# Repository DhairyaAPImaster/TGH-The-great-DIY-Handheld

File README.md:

# TGH - THE GREAT (DIY) HANDHELD
So yeah this is me trying to make my own custom retro handheld gaming device with a custom pcb powered by a pi zero 2w.

**BTW NOTE:** the case shall be printed by someone who was willing to print it from the slack channel - #printing-legion.

***very VERY IMPORTANT NOTE TO MACONDO REVIWER ---> SO IN THE BOM U MIGHT SEE THAT THE QTY OF SOME OF THE COMPONENTS FROM ROBU.IN IS MORE THAN REQUIRED THIS IS BECAUSE ROBU.IN HAS A MINIMUM ORDER QTY OF 10 INDIAN RUPEES PER COMPONENT SO HENCE I HAD TO LIKE INCREASE THE QTY OF SOME OF THE PASIVE COMPOENNTS TO LIKE FOLLOW THIS. BTW ITS STILL LIKE WAY WAY CHEAPER THAN JLCPCB'S PCBA THAT WOULD HAVE BROUGHT THE TOTAL COST TO 199.56 USD EXCLUDING TAX (I CHECKED)***

## project layout

```
.
├── `Assembly Layered.step`
├── `Assembly.step`
├── `wiring diagram.png`
├── `Custom Firmware!!!!!!!!!!/`
│   ├── `Launcher.py`
│   ├── `roms/`
│   │   ├── `GB/`
│   │   ├── `GBA/`
│   │   ├── `GBC/`
│   │   ├── `GEN/`
│   │   ├── `NES/`
│   │   ├── `SMS/`
│   │   └── `SNES/`
│   ├── `saves/`
│   └── `states/`
├── `production files/`
│   ├── `CAD/`
│   └── `PCB/`
│       ├── `MAIN PANELISED PCB (TO BE MANUFACTURED)/`
│       ├── `Mother board (not to be manufactured)/`
│       ├── `left daughter board (not to be manufactured)/`
│       └── `right daughter board (not to be manufactured)/`
└── `src/`
		├── `FreeCAD/`
		└── `PCB/`

```

## quick specs
- Panelised PCB Dimensions - 339.82 mm x 102.32 mm
- the only KiCAD plugin i used was KiKit to panelise the board, everything else was designed by me (this is my first major PCB project)

## WIRING DIAGRAM

## HOW TO RECREATE THIS PROJECT YOURSELF!!! 
- Step 1 - Basically Just Clone or downlaod this repo from github. U can do this by either going to the code button on this repo page and pressing download Zip or u can clone this Repo.
- Step 2 - Upload the gerbers zip file in JLCPCB (or any other manufacturer) Place order Page (u will need to sign up to order but can get a quote without signing up on jlcpcb)
- Step 3 - Change the colour of the PCB in the options JLC gives (if u use JLC PCB most of the times canging colours does not add any charge acc to what i know)
- Step 4 - Select PCBA if u want JLCPCB to assemble the PCB for you (though it is way more expensive than just soldering everything yourself.)
- Step 5 - Upload the CPL and BOM files.(if you are getting pcba)
- Step 6 - Recheck the position of all components
- Step 7 - Add to cart and order the PCB!! **(if you are soldering the components yourself you will need to buy them from some other place im mainly using robu.in and some components froma amzon and others)**
- Step 8 - If you dont have a 3D PRINTER jlcpcb has a 3d printing service too caled JLC3DP so u can upload the files for the case there and get it printed too but if u have a 3d printer you can just print it youreslf and save a lot of money.
- Step 9 - Order strong epoxy glue or superglue that does not cause harm to the 3d printed case material (I will be using FeviQuick as it should not cause harm to PLA in which the case will be printed)
- Step 10 - WAIT WAIT WAIT for your parts to be delhivered
- Step 11 - Once you have the PCB you will need to connect the daughter boards to the main motherboard using wires or an FFC connector i will be using solid code jumper wires since they are the easiest.
- Step 12 - If you are hand soldering the components you need to hand solder them according to the PCB Design that you can find by opening the project in kicad.
- Step 13 - Once you have all the parts ready (PCB, CASE and the appropriate Glue) place the PCB in the Case (you might have to trim the spacers down a bit as i made the spacers high so that they arent to small as i can always cut higher spacers down but can not extend spacers that are short.)  Use hot glue to secure the PCB onto the Spacers (btw if you have a smaller 3d printer you will have to like print the case in parts or diagonaly as it is slightly bigger than like the a1 mini and others of that size)
- Step 14 - Once the PCB is secured inside the case glue the Top Part of the Case shut after attatching the button caps onto the switches and adjusting the spacing of the screen.
- Step 15 - BOOM  THERE YOU HAVE IT THE PHYSICAL HARDWARE IS DONE NOW THE FIRMWARE.....

- Step 16 - To run the firmware first flash RASPBERRY PI OS onto the raspberry pi

- Step 17 - Put the microSD card into the Raspberry Pi Zero 2 W and power it on. Give it a little bit of time to boot for the first time. If you are using the Pi by itself for the initial setup, connect it to a display and keyboard so you can configure everything.

- Step 18 - Clone this repository onto the Raspberry PiThen enter the firmware folder:

	`TGH-The-great-DIY-Handheld/"Custom Firmware!!!!!!!!!!`

	The firmware folder should look something like this:
	```
	Custom Firmware!!!!!!!!!!
	├── Launcher.py
	├── roms/
	│   ├── GB/
	│   ├── GBA/
	│   ├── GBC/
	│   ├── GEN/
	│   ├── NES/
	│   ├── SMS/
	│   └── SNES/
	├── saves/
	└── states/
	```

 - Step 19 - If everything is working correctly, the TGH launcher should start.

 - ALMOST LAST STEP - ADD YOUR ROMS to there respective folders in the firmware folder
	Basically:

	Game Boy ROM → `GB/`

	Game Boy Advance ROM → `GBA/`

	Game Boy Color ROM → `GBC/`

	Genesis ROM → `GEN/`

	NES ROM → `NES/`

	Sega Master System ROM → `SMS/`

	SNES ROM → `SNES/`

- TRUE LAST STEP - CONNECT EVERYTHING TO THE CUSTOM PCB

- **RECOMMENDED** - Before closing the case, test:

Does the Pi boot?
Does the display work?
Does the launcher start?
Do the buttons work?
Do the joysticks work?
Does audio work?
Does the speaker work?
Does the headphone jack work?
Does the power system work?
Do games launch?
Do saves/states work?

If all of those work (IF U DO IT CORRECTLY IT WILL WORK) THEN..... 
## BOOM!!!! YOU HAVE A WORKING RETRO HANDHELD GAMING DEVICE!!!!!!

## BOM/BILL OF MATERIALS (PARTS I NEED FUNDING FOR)

| Name | Purpose | Quantity | Total Cost (USD) | Link | Distributor |
|---|---|---|---|---|---|
| PCB from JLCPCB  | it is the main PCB and will connect all components to each other. (btw JLCPCB has min order qty for PCB as 5 so yeah) | 5 | 18.4 | https://cart.jlcpcb.com/ | JLCPCB |
| Raspberry Pi Zero | its basically the core of the whole project it shall basically run everything. | 1 | 19.08 | https://robu.in/product/raspberry-pi-zero-wireless-wh-pre-soldered-header/ | robu.in |
| 5 Inch Touch Screen HDMI Interface TFT LCD | to display. | 1 | 26.18 | https://robu.in/product/5-inch-touch-screen-hdmi-interface-display-module-tft-lcd-800x480-raspberry-pi-2-model-b-touch-pen/ | robu.in |
| Mini HDMI To HDMI Cable | to connect pi to display | 1 | 1.08 | https://robu.in/product/mini-hdmi-hdmi-cable-1-8-meter-round-high-quality-copper-clad-steel-black/ | robu.in |
| 10 uF capacitor | to decouple more  | 15 | 0.14 | https://robu.in/product/cs2012x7r106m100nre-samwha-10v-10uf-x7r-%c2%b120-0805-multilayer-ceramic-capacitors-mlcc-smd-smt-rohs/ | robu.in |
| 100nF capacitor | to decouple | 20 | 0.14 | https://robu.in/product/tcc0805x7r104k500dt-cctc-smt-ceramic-capacitors-0805-x7r-104k100nf%c2%b110-rated-voltage50v-thickness0-85mmtape/ | robu.in |
| 6x6x5mm tactile switches | to well be used as switches and for the buttons controlling everything. | 10 | 0.14 | https://robu.in/product/6x6x5mm-tactile-push-button-switch-pack-of-20/ | robu.in |
| MAX98358ETE | audio amplifier | 1 | 2.62 | https://robu.in/product/1-month-warranty-560/ | robu.in |
| MT3608  IC | to take a lower DC voltage and steps it up to a higher, adjustable DC voltage | 2 | 0.28 | https://robu.in/product/mt3608-xian-aerosemi-tech-boost-type-adjustable-2a-2v24v-sot-23-6-dc-dc-converters-rohs/ | robu.in |
| 33 µH BOURNS-SRR1260-330M-Power Inductor (SMD) | to stores energy in a magnetic field and resists changes in electrical current. | 1 | 0.67 | https://robu.in/product/srr1260-330m-bourns-srr1260-330m-power-inductor-smd-33-%c2%b5h-3-a-shielded-2-8-a-srr1260-series/ | robu.in |
| SOD-123 Schottky Diodes ROHS | used to allow current to flow in one direction. | 2 | 0.12 | https://robu.in/product/1n5819w-kexin-40v-600mv1a-1a-sod-123-schottky-diodes-rohs/ | robu.in |
| 100 ohm resistor | to resist current | 25 | 0.12 | https://robu.in/product/rc0805jr-07100rl-yageo-res-thick-film-0805-100-ohm-5-0-125w1-8w-%c2%b1100ppm-c-pad-smd-t-r/ | robu.in |
| 4.7k ohm resistor | to resist  | 29 | 0.12 | https://robu.in/product/yageo-4-7k-ohm-1-4w-0805-surface-mount-resistor-pack-of-50/ | robu.in |
| 10k ohm resistor | im legit tired of writing the same thing again for all the resistor but anyways ---> IT resists the flow of current. | 20 | 0.12 | https://robu.in/product/rc0805fr-0710kl-yageo-res-thick-film-0805-10k-ohm-1-0-125w1-8w-%c2%b1100ppm-c-pad-smd-t-r/ | robu.in |
| 20k ohm resistor | u are not gonna belive what this does ---> IT resists the flow of current.... | 29 | 0.12 | https://robu.in/product/rc0805fr-0720kl-yageo-res-thick-film-0805-20k-ohm-1-0-125w1-8w-%c2%b1100ppm-c-pad-smd-t-r/ | robu.in |
| 33k ohm resistor | to resist!!!!! | 20 | 0.12 | https://robu.in/product/rc0805fr-0733kl-yageo-res-thick-film-0805-33k-ohm-1-0-125w1-8w-%c2%b1100ppm-c-pad-smd-t-r/ | robu.in |
| 100k ohm 0805 resistor | to resist flow of current? | 23 | 0.12 | https://robu.in/product/yageo-100k-ohm-1-2w-0805-surface-mount-resistor-pack-of-50/ | robu.in |
| D6.3xL11mm Aluminum Electrolytic Capacitors | its a capacitor dude like it provides capacitance (idk what do i write under Purpose) | 4 | 0.18 | https://robu.in/product/16yxf100mefct16-3x11-rubycon-100uf-16v-%c2%b120-plugind6-3xl11mm-aluminum-electrolytic-capacitors-leaded-rohs/ | robu.in |
| 22µF SMT 0805 capacitor | To provide capacitance | 10 | 0.18 | https://robu.in/product/tcc0805x5r226k100ft-cctc-smt-ceramic-capacitors-0805-x5r-226k22%c2%b5f%c2%b110-rated-voltage10v-thickness1-25mmtape/ | robu.in |
| TP4056 1A Li-Ion Battery Charging Board | To charge the battery  | 1 | 0.17 | https://robu.in/product/tp4056-1a-li-ion-battery-charging-board-micro-usb-with-current-protection-type-c-connector/ | Robu.in |
| 1mm Pitch Pin headers | These are seperate as the previous headers are not 1mm pitch pin headers. | 1 | 0.21 | https://robu.in/product/1-month-warranty-884/ | Robu.in |
| 3.5mm Female Audio Jack Connector  | to attach headphones | 1 | 0.47 | https://evelta.com/3-5mm-female-audio-jack-connector-6pin-1/ | Evelta.com |
| ADS1115IDGSR - 16-Bit ADC 2, 4 Input 1 Sigma-Delta IC VSSOP-10 | to convert analog voltage signals into digital data  | 1 | 1.94 | https://evelta.com/ads1115idgsr-16-bit-adc-2-4-input-1-sigma-delta-ic-vssop-10/ | Evelta.com |
| PS2 Game Joystick Module | For the Joysticks | 2 | 0.82 | https://www.flyrobo.in/ps2_game_joystick_module_for_arduino | FlyRobo |
| Male and Female Header Connector Strip, Pack of 10, Breakable Strip | For the pin Headers (btw this was a cheap pack of 10 and is actually cheaper than buying each header individually) | 1 | 1.27 | https://www.amazon.in/gp/product/B0FQP3SN7H/ref=ox_sc_act_image_8?smid=ATNZHHWX66S9H&psc=1 | Amazon |
| SPDT Slide Switch Right Angle | TO turn on and off | 1 | 1.0 | https://www.amazon.in/gp/product/B0B434R6QF/ref=ox_sc_act_image_7?smid=A2JDRZEGU1IDE2&psc=1 | Amazon |
| 0.5Watt Power Audio Speaker | For sound | 1 | 1.21 | https://www.amazon.in/gp/product/B07MTK843Z/ref=ox_sc_act_image_6?smid=AJ6SIZC8YQDZX&psc=1 | Amazon |
| Isopropyl Alcohol | For cleaning Board after soldering. | 1 | 2.95 | https://www.amazon.in/gp/product/B0DXLCF467/ref=ox_sc_act_image_5?smid=A66YHFPLB5NLO&th=1 | Amazon |
| Tactile Push Button Switch Caps | To button | 1 | 2.34 | https://www.amazon.in/gp/product/B0DCP7J7R7/ref=ox_sc_act_image_4?smid=AOG7U64E0DVL2&psc=1 | Amazon |
| Jumper Wires | For fine adjustment if required | 1 | 1.66 | https://www.amazon.in/gp/product/B0CPFCRCHB/ref=ox_sc_act_image_3?smid=AJ6SIZC8YQDZX&th=1 | Amazon |
| Solder  | to solder | 1 | 8.37 | https://www.amazon.in/gp/product/B084RZWVXY/ref=ox_sc_act_image_2?smid=AVIYBMAJK8N56&th=1 | Amazon |
| Soldering Flux | Helping to solder. | 1 | 0.84 | https://www.amazon.in/gp/product/B0FV8HHBTN/ref=ox_sc_act_image_1?smid=A366YFPXO3CTI5&psc=1 | Amazon |

## fab note
- so i plan on using JLCPCB to actually get my boards manufactured (i checked and for the size of this project's pcb getting the pcb from robu.in is way more expensive than jlcpcb) but will be ASSEMBLING THE COMPONENTS BY HAND!!!!

## pics from while i was designing it

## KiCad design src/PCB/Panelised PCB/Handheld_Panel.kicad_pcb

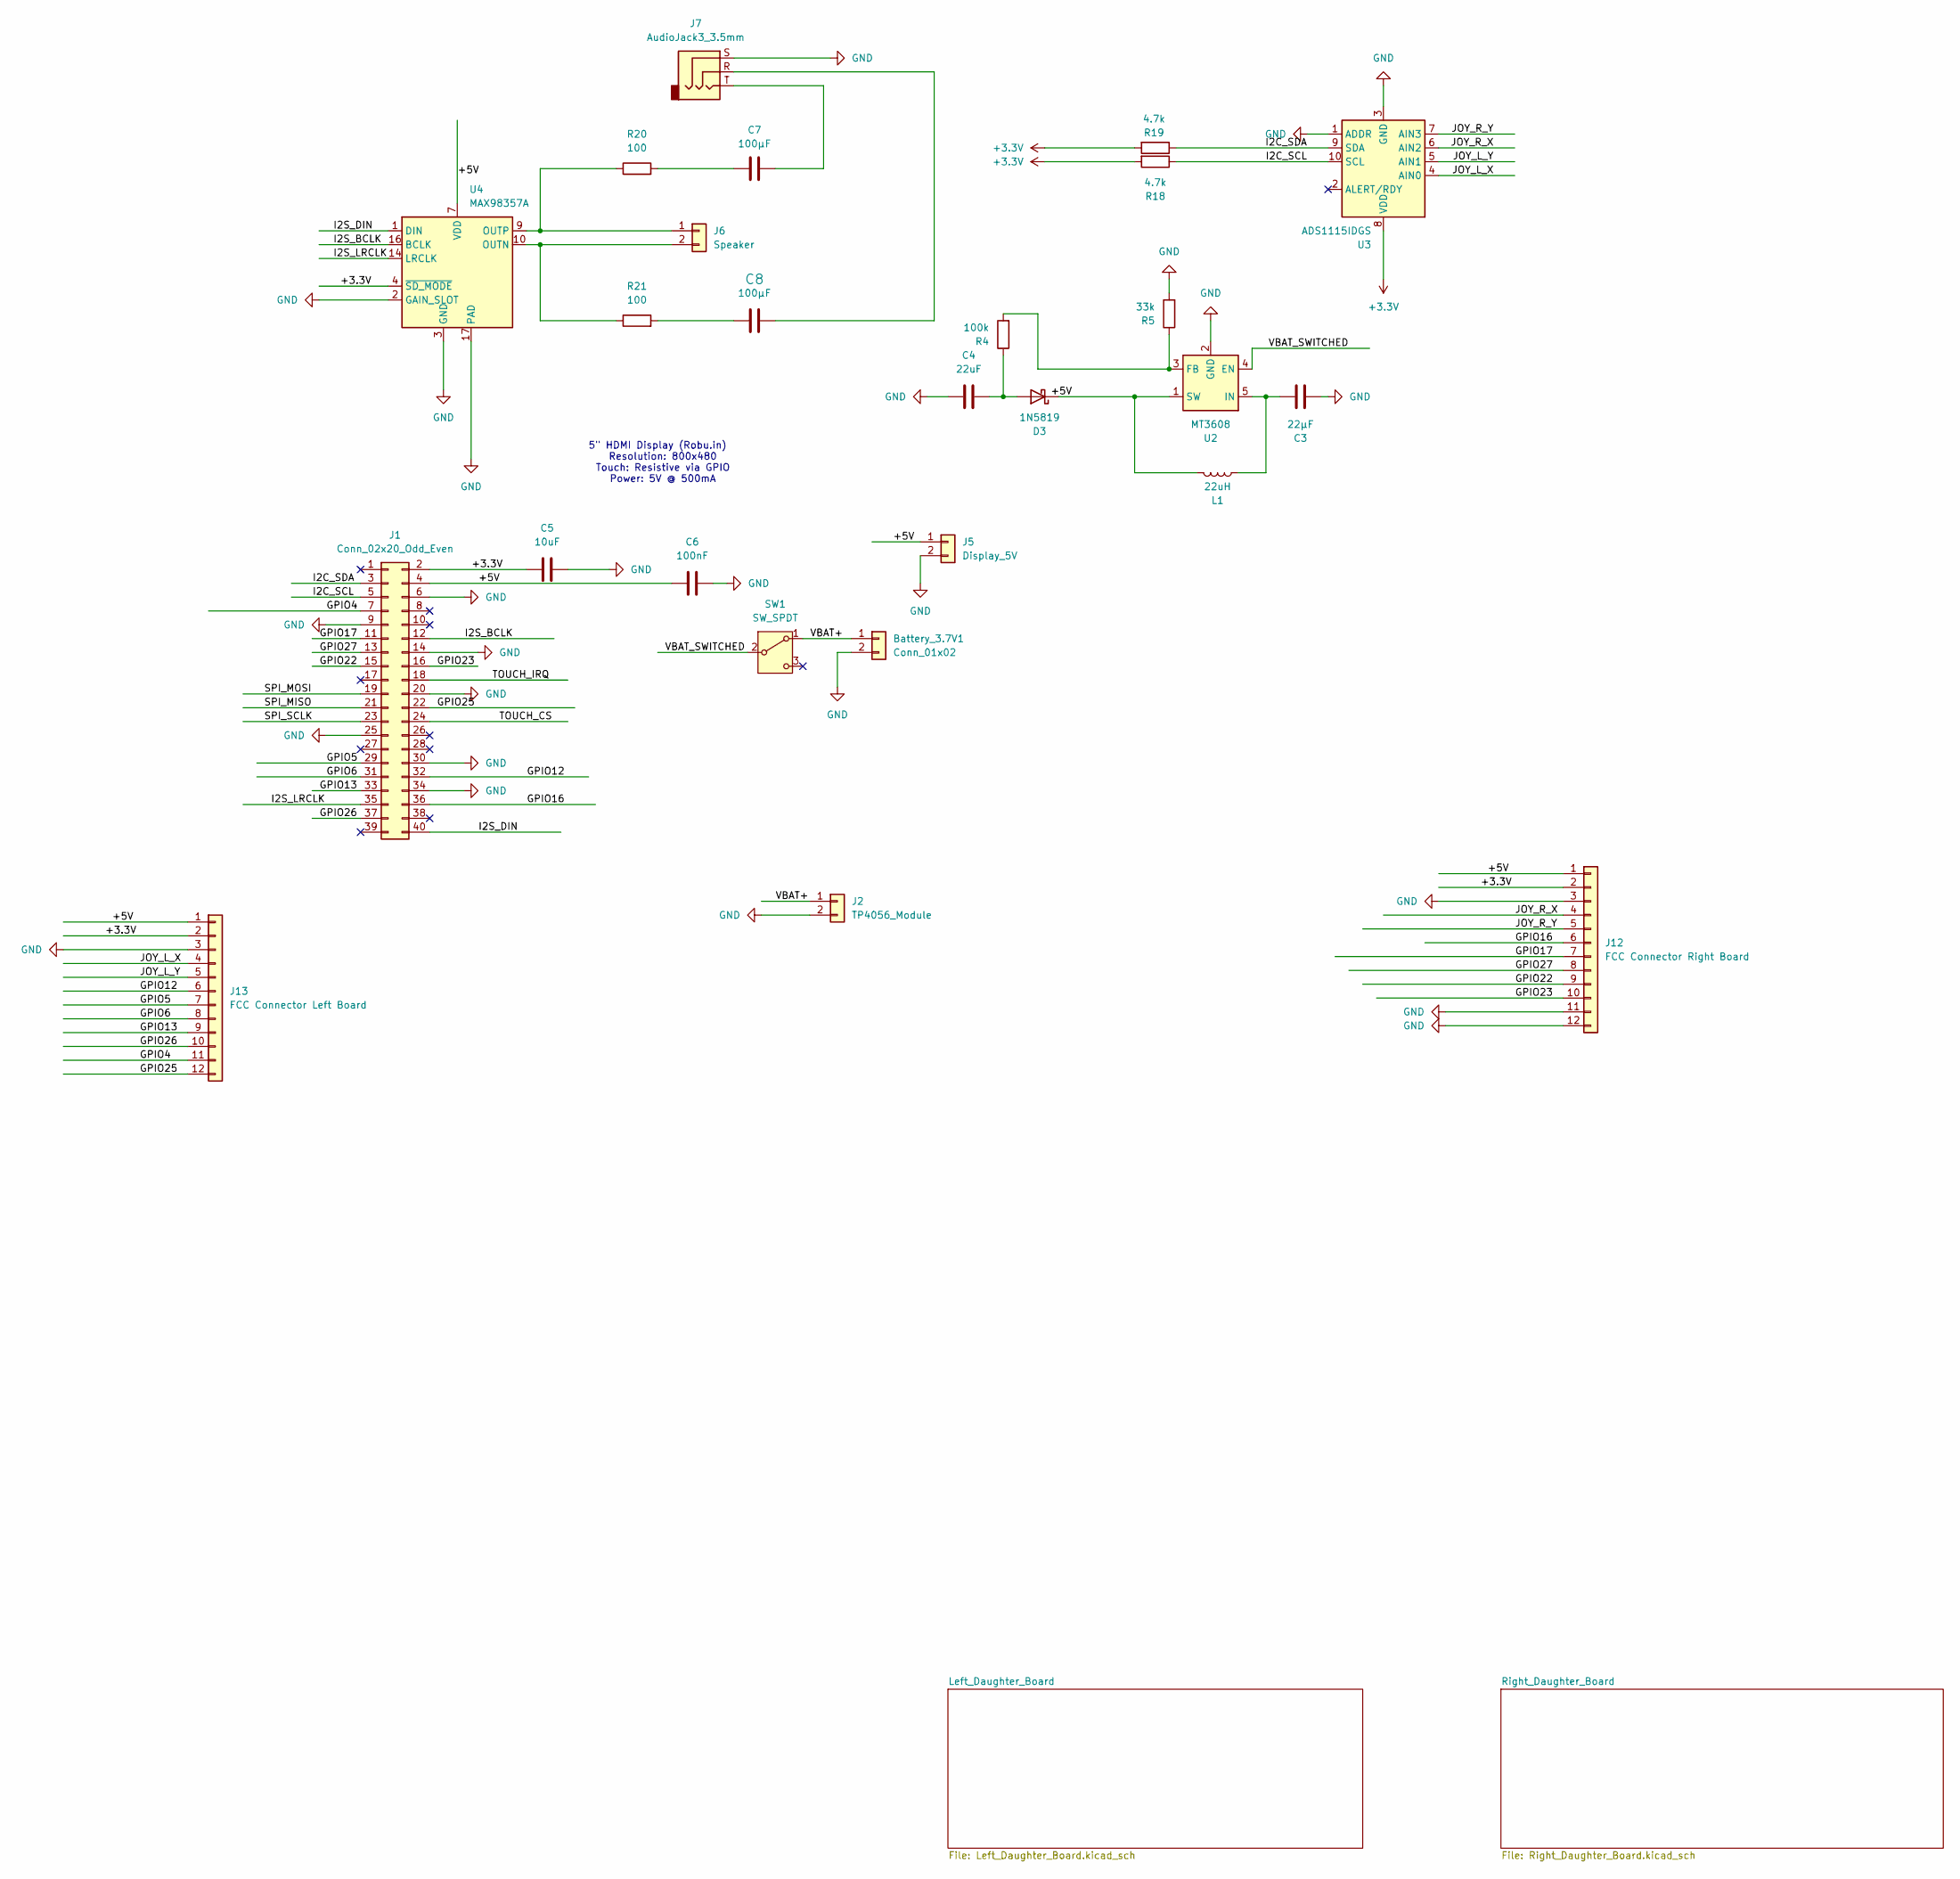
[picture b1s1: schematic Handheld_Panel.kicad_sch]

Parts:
Battery_3.7V1: Conn_01x02; PinHeader_1x02_P2.54mm_Vertical
C3: 22µF; C_0805_2012Metric
C4: 22uF; C_0805_2012Metric
C5: 10uF; C_0805_2012Metric
C6: 100nF; C_0805_2012Metric
C7, C8: 100µF; CP_Radial_D6.3mm_P2.50mm
D3: 1N5819; D_SOD-123
J1: Conn_02x20_Odd_Even; PinHeader_2x20_P2.54mm_Vertical
J2: TP4056_Module; PinHeader_1x02_P2.54mm_Vertical
J5: Display_5V; PinHeader_1x02_P2.54mm_Vertical
J6: Speaker; PinHeader_1x02_P2.54mm_Vertical
J7: AudioJack3_3.5mm; Jack_3.5mm_CUI_SJ-3523-SMT_Horizontal
J12: FCC Connector Right Board; PinHeader_1x12_P1.00mm_Vertical
J13: FCC Connector Left Board; PinHeader_1x12_P1.00mm_Vertical
L1: 22uH; L_Bourns_SRR1260
R4: 100k; R_0805_2012Metric
R5: 33k; R_0805_2012Metric
R18, R19: 4.7k; R_0805_2012Metric
R20, R21: 100; R_0805_2012Metric
SW1: SW_SPDT; SW_Slide_SPDT_Angled_CK_OS102011MA1Q
U2: MT3608; SOT-23-6
U3: ADS1115IDGS; TSSOP-10_3x3mm_P0.5mm
U4: MAX98357A; TQFN-16-1EP_3x3mm_P0.5mm_EP1.23x1.23mm

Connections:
+3.3V: C5.1, J1.2, J12.2, J13.2, R18.2, R19.2, U3.8 (VDD), U4.4 (~SD_MODE); also elsewhere on the board
/+5V: C6.1, D3.1 (K), J1.4, J5.1, J12.1, J13.1, L1.2, U2.1 (SW), U4.7 (VDD), U4.8 (VDD)
/GPIO4: J1.7, J13.11
/GPIO5: J1.29, J13.7
/GPIO6: J1.31, J13.8
/GPIO12: J1.32, J13.6
/GPIO13: J1.33, J13.9
/GPIO16: J1.36, J12.6
/GPIO17: J1.11, J12.7
/GPIO22: J1.15, J12.9
/GPIO23: J1.16, J12.10
/GPIO25: J1.22, J13.12
/GPIO26: J1.37, J13.10
/GPIO27: J1.13, J12.8
/I2C_SCL: J1.5, R18.1, U3.10 (SCL)
/I2C_SDA: J1.3, R19.1, U3.9 (SDA)
/I2S_BCLK: J1.12, U4.16 (BCLK)
/I2S_DIN: J1.40, U4.1 (DIN)
/I2S_LRCLK: J1.35, U4.14 (LRCLK)
/JOY_L_X: J13.4, U3.4 (AIN0)
/JOY_L_Y: J13.5, U3.5 (AIN1)
/JOY_R_X: J12.4, U3.6 (AIN2)
/JOY_R_Y: J12.5, U3.7 (AIN3)
/SPI_MISO: J1.21
/SPI_MOSI: J1.19
/SPI_SCLK: J1.23
/TOUCH_CS: J1.24
/TOUCH_IRQ: J1.18
/VBAT+: Battery_3.7V1.1, J2.1, SW1.1 (A)
/VBAT_SWITCHED: SW1.2 (B), U2.4 (EN)
GND: Battery_3.7V1.2, C3.1, C4.2, C5.2, C6.2, J1.6, J1.9, J1.14, J1.20, J1.25, J1.30, J1.34, J2.2, J5.2, J7.S, J12.3, J12.11, J12.12, J13.3, R5.2, U2.2 (GND), U3.1 (ADDR), U3.3 (GND), U4.2 (GAIN_SLOT), U4.3 (GND), U4.11 (GND), U4.15 (GND), U4.17 (PAD); also elsewhere on the board
unnamed: C7.1, R20.2
unnamed: C7.2, J7.T
unnamed: C8.1, R21.2
unnamed: C8.2, J7.R
unnamed: C4.1, D3.2 (A), R4.1
unnamed: J6.1, R20.1, U4.9 (OUTP)
unnamed: J6.2, R21.1, U4.10 (OUTN)
unnamed: R4.2, R5.1, U2.3 (FB)
unnamed: C3.2, L1.1, U2.5 (IN)

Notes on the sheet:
5" HDMI Display (Robu.in) Resolution: 800x480 Touch: Resistive via GPIO Power: 5V @ 500mA

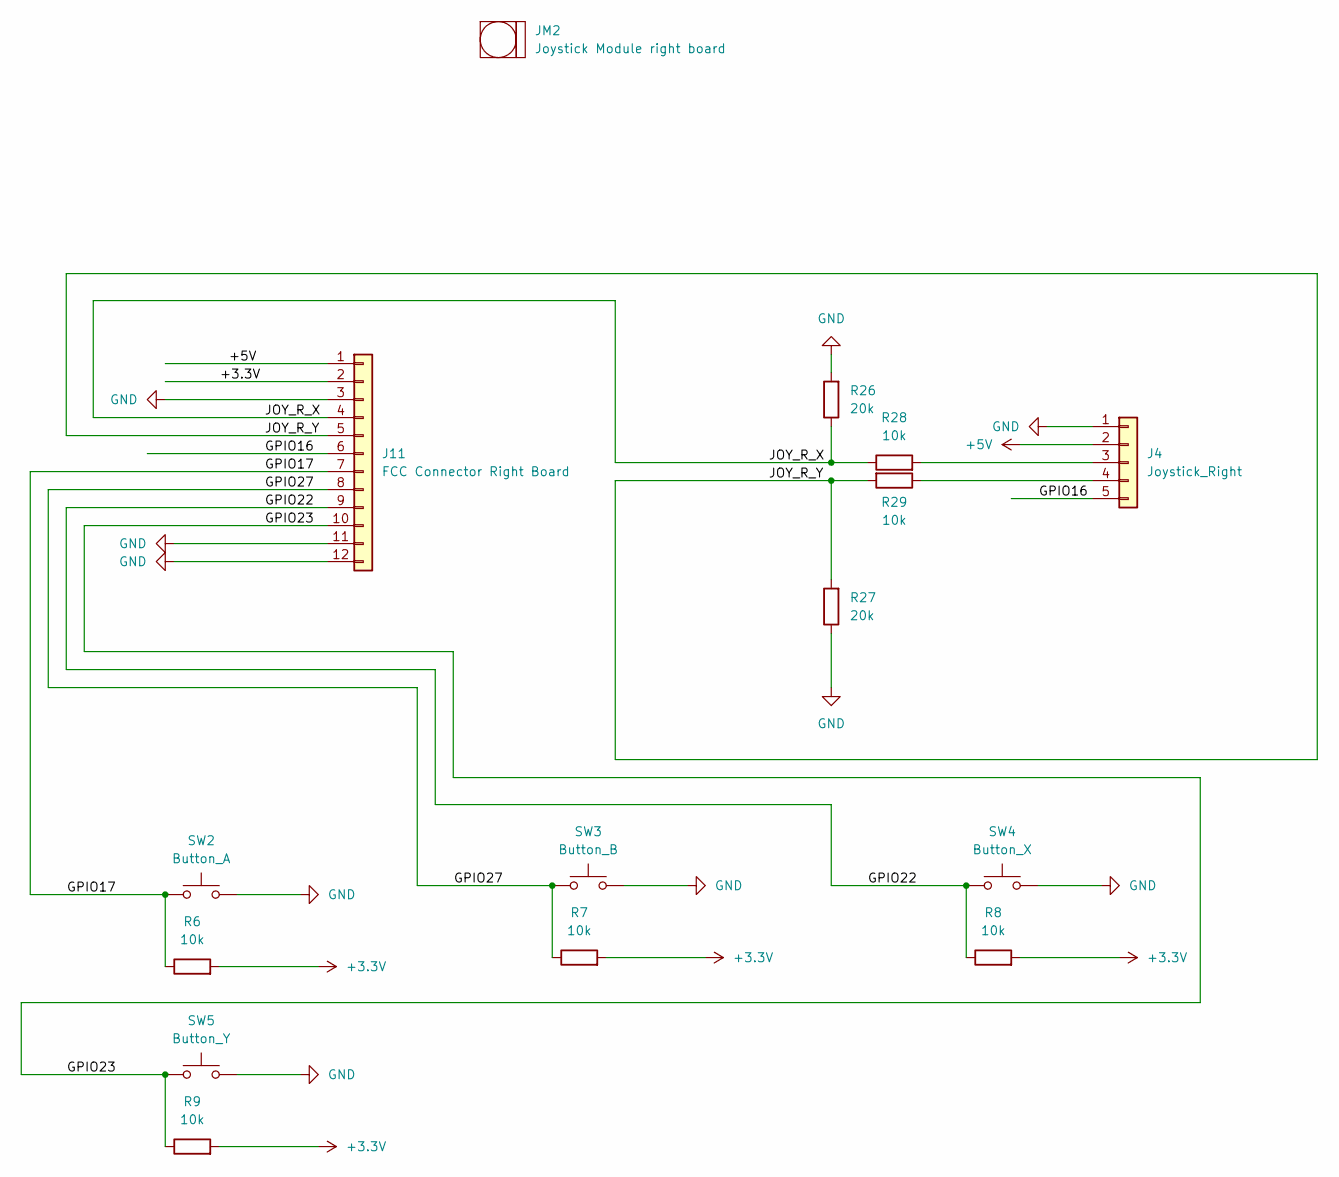
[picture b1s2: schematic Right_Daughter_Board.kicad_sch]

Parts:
J4: Joystick_Right; PinSocket_1x05_P2.54mm_Horizontal
J11: FCC Connector Right Board; PinHeader_1x12_P1.00mm_Vertical
JM2: Joystick Module right board; Joystick Module 40x27mm
R6, R7, R8, R9, R28, R29: 10k; R_0805_2012Metric
R26, R27: 20k; R_0805_2012Metric
SW2: Button_A; SW_PUSH_6mm_H5mm
SW3: Button_B; SW_PUSH_6mm_H5mm
SW4: Button_X; SW_PUSH_6mm_H5mm
SW5: Button_Y; SW_PUSH_6mm_H5mm

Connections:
+3.3V: J11.2, R6.2, R7.2, R8.2, R9.2; also elsewhere on the board
+5V: J4.2, J11.1; also elsewhere on the board
/Right_Daughter_Board/GPIO16: J4.5, J11.6
/Right_Daughter_Board/GPIO17: J11.7, R6.1, SW2.1
/Right_Daughter_Board/GPIO22: J11.9, R8.1, SW4.1
/Right_Daughter_Board/GPIO23: J11.10, R9.1, SW5.1
/Right_Daughter_Board/GPIO27: J11.8, R7.1, SW3.1
/Right_Daughter_Board/JOY_R_X: J11.4, R26.1, R28.1
/Right_Daughter_Board/JOY_R_Y: J11.5, R27.2, R29.2
GND: J4.1, J11.3, J11.11, J11.12, R26.2, R27.1, SW2.2, SW3.2, SW4.2, SW5.2; also elsewhere on the board
unnamed: J4.3, R28.2
unnamed: J4.4, R29.1

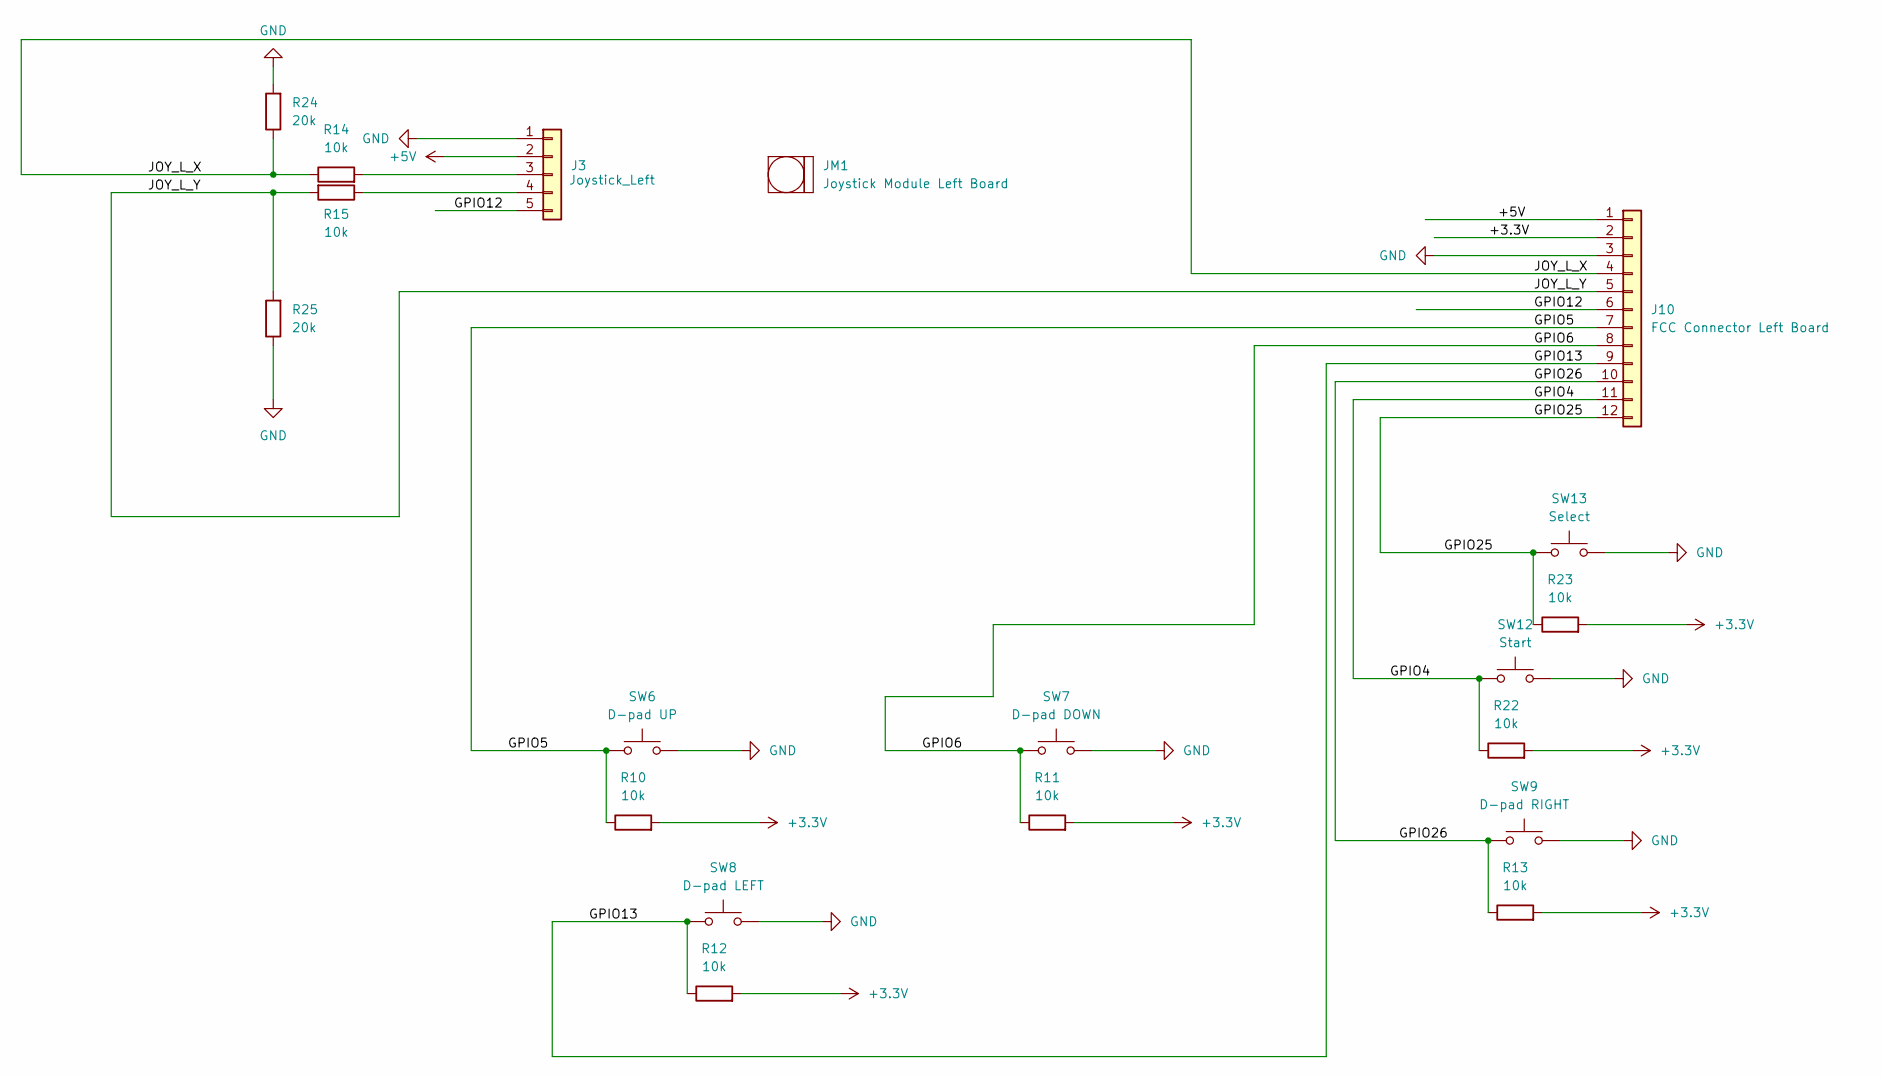
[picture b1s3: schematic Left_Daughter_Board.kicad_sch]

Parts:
J3: Joystick_Left; PinSocket_1x05_P2.54mm_Horizontal
J10: FCC Connector Left Board; PinHeader_1x12_P1.00mm_Vertical
JM1: Joystick Module Left Board; Joystick Module 40x27mm
R10, R11, R12, R13, R14, R15, R22, R23: 10k; R_0805_2012Metric
R24, R25: 20k; R_0805_2012Metric
SW6: D-pad UP; SW_PUSH_6mm_H5mm
SW7: D-pad DOWN; SW_PUSH_6mm_H5mm
SW8: D-pad LEFT; SW_PUSH_6mm_H5mm
SW9: D-pad RIGHT; SW_PUSH_6mm_H5mm
SW12: Start; SW_PUSH_6mm_H5mm
SW13: Select; SW_PUSH_6mm_H5mm

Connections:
+3.3V: J10.2, R10.2, R11.2, R12.2, R13.2, R22.2, R23.2; also elsewhere on the board
+5V: J3.2, J10.1; also elsewhere on the board
/Left_Daughter_Board/GPIO4: J10.11, R22.1, SW12.1
/Left_Daughter_Board/GPIO5: J10.7, R10.1, SW6.1
/Left_Daughter_Board/GPIO6: J10.8, R11.1, SW7.1
/Left_Daughter_Board/GPIO12: J3.5, J10.6
/Left_Daughter_Board/GPIO13: J10.9, R12.1, SW8.1
/Left_Daughter_Board/GPIO25: J10.12, R23.1, SW13.1
/Left_Daughter_Board/GPIO26: J10.10, R13.1, SW9.1
/Left_Daughter_Board/JOY_L_X: J10.4, R14.1, R24.1
/Left_Daughter_Board/JOY_L_Y: J10.5, R15.2, R25.2
GND: J3.1, J10.3, R24.2, R25.1, SW6.2, SW7.2, SW8.2, SW9.2, SW12.2, SW13.2; also elsewhere on the board
unnamed: J3.3, R14.2
unnamed: J3.4, R15.1

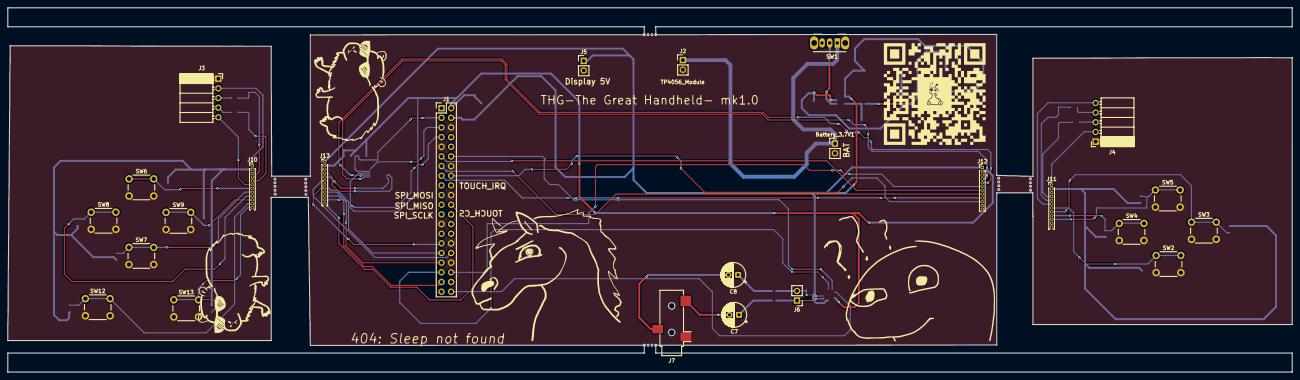
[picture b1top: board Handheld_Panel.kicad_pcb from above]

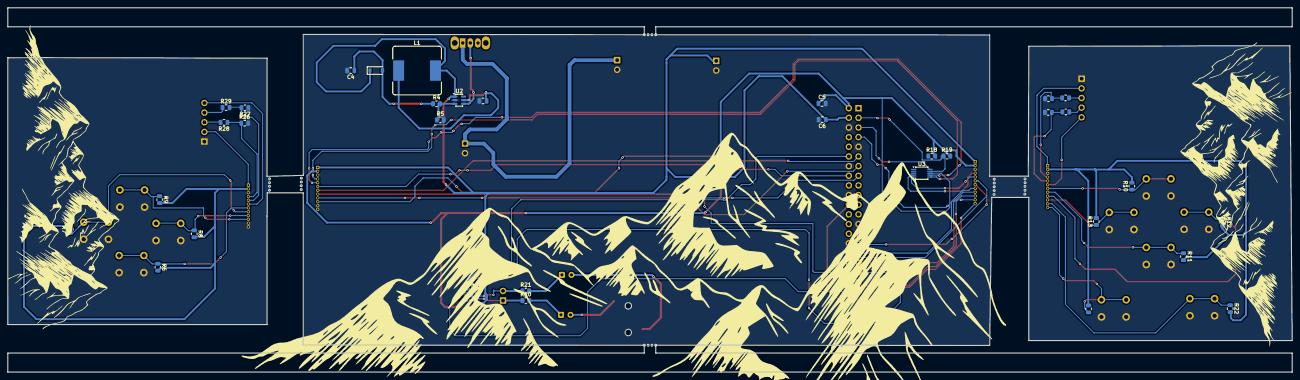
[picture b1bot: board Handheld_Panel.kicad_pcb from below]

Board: 2 copper layers, 337.8 x 95.8 mm, 85 parts (34 on the bottom side), 56 nets.

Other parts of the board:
KiKit_MB_1_1, KiKit_MB_1_2, KiKit_MB_1_2#2, KiKit_MB_1_2#3, KiKit_MB_1_2#4, KiKit_MB_1_2#5, KiKit_MB_1_2#6, KiKit_MB_1_2#7, KiKit_MB_1_2#8, KiKit_MB_1_2#9, KiKit_MB_1_3, KiKit_MB_1_3#2, KiKit_MB_1_3#3, KiKit_MB_1_3#4, KiKit_MB_1_3#5, KiKit_MB_1_3#6, KiKit_MB_1_3#7, KiKit_MB_1_3#8, KiKit_MB_1_3#9, KiKit_MB_1_3#10, KiKit_MB_1_3#11, KiKit_MB_1_4, KiKit_MB_2_1, KiKit_MB_2_2, KiKit_MB_2_3, KiKit_MB_2_4: NPTH
g: LOGO

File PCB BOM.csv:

"Id","Designator","Footprint","Quantity","Designation","Supplier and ref"
1,"Battery_3.7V1","PinHeader_1x02_P2.54mm_Vertical",1,"Conn_01x02",""
2,"C1","C_0805_2012Metric",1,"10µF",""
3,"C2","C_0805_2012Metric",1,"4.7µF",""
4,"C3","C_0805_2012Metric",1,"22µF",""
5,"C4","C_0805_2012Metric",1,"22uF",""
6,"C5","C_0805_2012Metric",1,"10uF",""
7,"C6","C_0402_1005Metric",1,"100nF",""
8,"C7, C8","CP_Radial_D6.3mm_P2.50mm",2,"100µF",""
9,"D1","LED_D3.0mm",1,"RED",""
10,"D2","LED_D3.0mm",1,"Green",""
11,"D3","D_SOD-123",1,"1N5819",""
12,"J1","PinHeader_2x20_P2.54mm_Vertical",1,"Conn_02x20_Odd_Even",""
13,"J2","USB_C_Receptacle_GCT_USB4085",1,"USB_C_Receptacle_USB2.0_14P",""
14,"J3","PinSocket_1x05_P2.54mm_Horizontal",1,"Joystick_Left",""
15,"J4","PinSocket_1x05_P2.54mm_Horizontal",1,"Joystick_Right",""
16,"J5","PinHeader_1x02_P2.54mm_Vertical",1,"Display_5V",""
17,"J6","PinHeader_1x02_P2.54mm_Vertical",1,"Speaker",""
18,"J7","Jack_3.5mm_CUI_SJ-3523-SMT_Horizontal",1,"AudioJack3_3.5mm",""
19,"J10, J13","PinHeader_1x12_P1.00mm_Vertical",2,"FCC Connector Left Board",""
20,"J11, J12","PinHeader_1x12_P1.00mm_Vertical",2,"FCC Connector Right Board",""
21,"JM1","Joystick Module 40x27mm",1,"Joystick Module Left Board",""
22,"JM2","Joystick Module 40x27mm",1,"Joystick Module right board",""
23,"L1","L_Bourns_SRR1260",1,"22uH",""
24,"R1","R_0402_1005Metric",1,"2K",""
25,"R2, R3","R_0402_1005Metric",2,"1K",""
26,"R4","R_0402_1005Metric",1,"100k",""
27,"R5","R_0402_1005Metric",1,"33k",""
28,"R6, R7, R8, R9, R10, R11, R12, R13, R14, R15, R22, R23, R28, R29","R_0402_1005Metric",14,"10k",""
29,"R16, R17","R_0402_1005Metric",2,"5.1k",""
30,"R18, R19","R_0402_1005Metric",2,"4.7k",""
31,"R20, R21","R_0402_1005Metric",2,"100",""
32,"R24, R25, R26, R27","R_0402_1005Metric",4,"20k",""
33,"SW1","SW_Slide_SPDT_Angled_CK_OS102011MA1Q",1,"SW_SPDT",""
34,"SW2","SW_PUSH_6mm_H5mm",1,"Button_A",""
35,"SW3","SW_PUSH_6mm_H5mm",1,"Button_B",""
36,"SW4","SW_PUSH_6mm_H5mm",1,"Button_X",""
37,"SW5","SW_PUSH_6mm_H5mm",1,"Button_Y",""
38,"SW6","SW_PUSH_6mm_H5mm",1,"D-pad UP",""
39,"SW7","SW_PUSH_6mm_H5mm",1,"D-pad DOWN",""
40,"SW8","SW_PUSH_6mm_H5mm",1,"D-pad LEFT",""
41,"SW9","SW_PUSH_6mm_H5mm",1,"D-pad RIGHT",""
42,"SW12","SW_PUSH_6mm_H5mm",1,"Start",""
43,"SW13","SW_PUSH_6mm_H5mm",1,"Select",""
44,"U1","SOIC-8-1EP_3.9x4.9mm_P1.27mm_EP2.41x3.3mm_ThermalVias",1,"TP4056-42-ESOP8",""
45,"U2","SOT-23-6",1,"MT3608",""
46,"U3","TSSOP-10_3x3mm_P0.5mm",1,"ADS1115IDGS",""
47,"U4","TQFN-16-1EP_3x3mm_P0.5mm_EP1.23x1.23mm",1,"MAX98357A",""

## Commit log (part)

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2026-05-12 Main
2026-05-12 changed the folder description to be more descriptive ig
2026-05-12 Revise README with project specs and BOM
    Updated project details, specifications, and components list for the DIY handheld gaming device.
2026-05-12 Fix formatting issues in PCB BOM.csv
    Updated the PCB BOM file to correct formatting and ensure proper CSV structure.
2026-05-14 changed the PCB to use the module instead of the chip
2026-05-14 Update README with case printing note
    Added note about case printing from Slack channel.
2026-05-14 Clarify description for 6mm Tactile Buttons
    Updated the description for the 6mm Tactile Buttons.
2026-05-14 fixed the BOM
2026-05-14 fixed the BOM and added details to the 3d case.
2026-05-14 final commit fixed BOM
2026-05-14 updated BOM
2026-05-14 added art on my PCB including a capybara and a horse that i drew myself!!!
2026-05-14 fixed the orientation of the pcb art
2026-05-14 finally fixed the art on the PCB
2026-05-14 ok this time i finally fixed it with the mountains art on the back.
2026-05-14 last time i forgot to add the qr code on the PCB now it is there!!
2026-05-16 added custom firmware that shall run ontop of PiOS Lite as it has - RetroArch (emulators), Auto-start on boot, and can run my python launcher making a perfect handheld gaming device with custom firmw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
2026-05-16 Added a custom python firmware. Also made changes to the 3d Model to include the holes for the joysticls too!
2026-05-16 fixed the firmware.
2026-06-16 changed the project structure to be organised and updated readME
2026-06-24 ADDED VERY VERY IMPORTANT NOTE FOR STASIS PROJECT REVIEWER.
    Added important notes regarding PCBA and hand soldering limitations due to upcoming exams.
2026-06-24 fixed wrong PCB and PCBA price in the ReadME
2026-06-27 arranged the folder structure in a manner that is actually presentable.
2026-06-27 updated the folder structure in the ReadMe.
2026-06-27 fixed errors in like the PCB that i just now noticed
2026-06-27 fixed stuff in the panelised PCB---> fixed the traces as many MANY were at like 90 degree angles and were kindoff messed up then also updated resistors and capacitors to 0805 size as i am planning on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
2026-06-28 Revise BOM and assembly notes in README
    Updated BOM section to clarify component quantities and costs. Added notes regarding assembly and sourcing components.
2026-06-28 added .stl files
